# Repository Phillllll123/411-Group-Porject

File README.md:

# 411-Group-Porject
Group 3
git add

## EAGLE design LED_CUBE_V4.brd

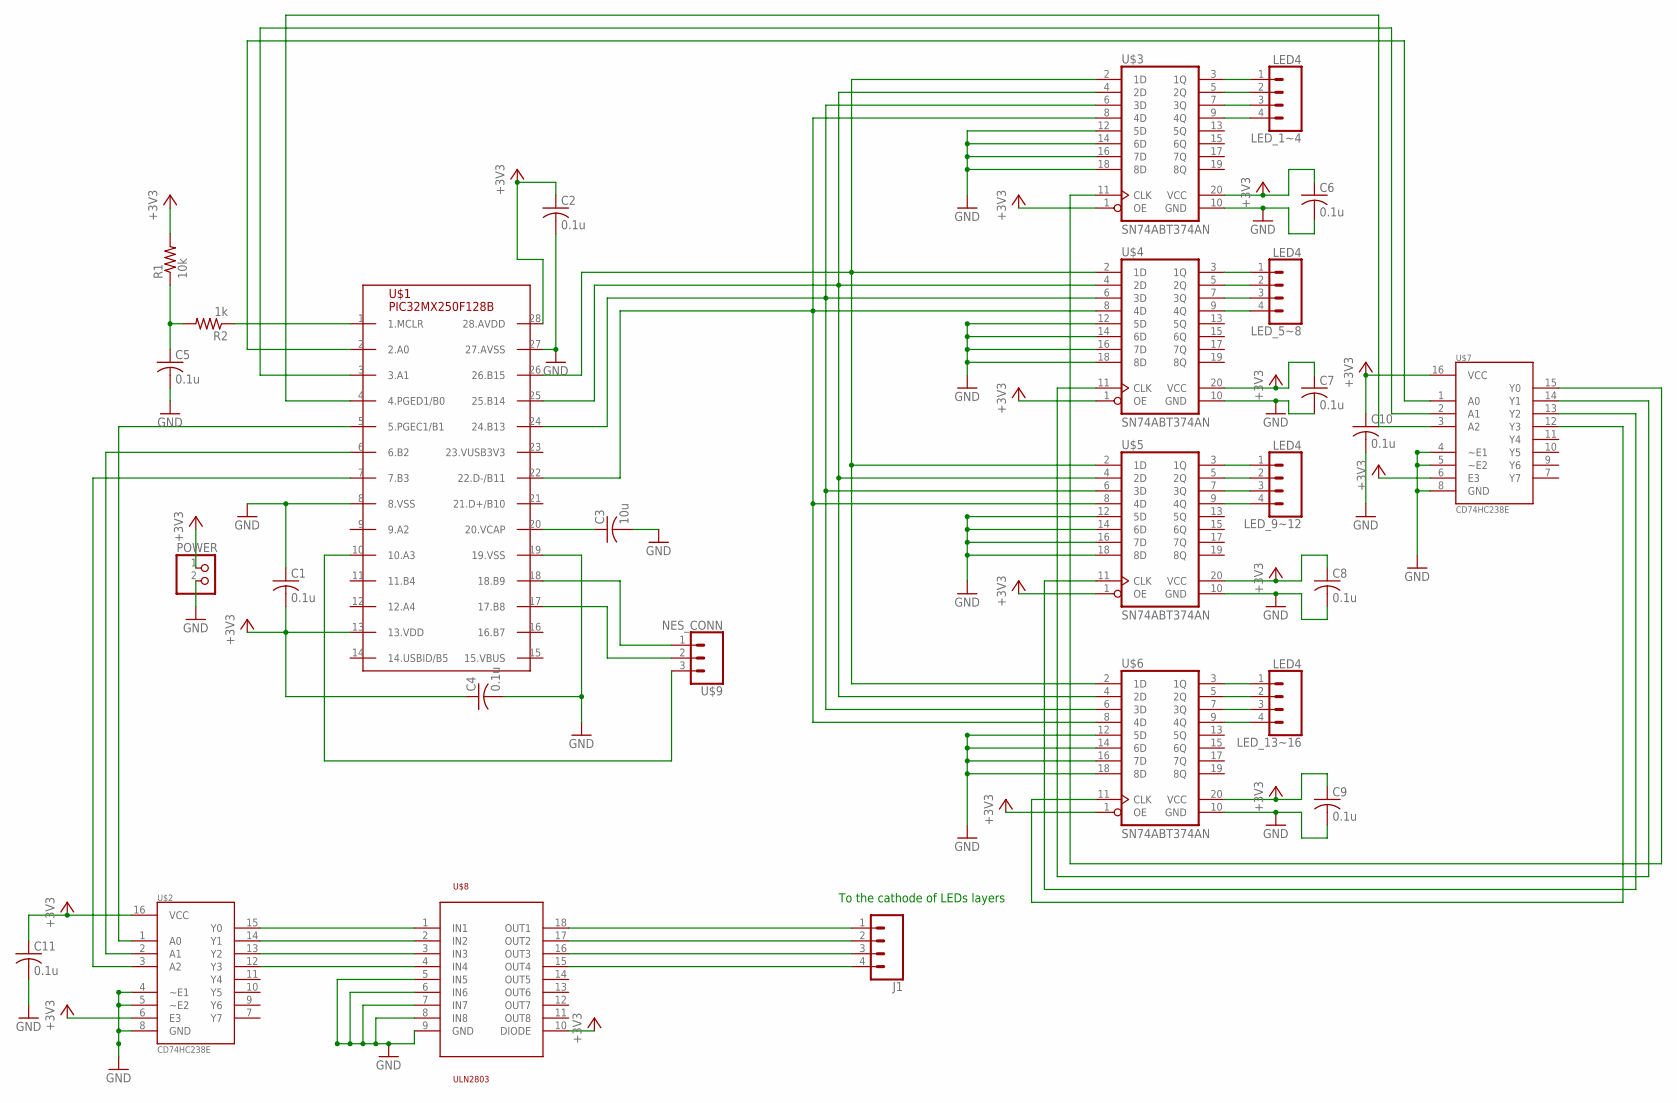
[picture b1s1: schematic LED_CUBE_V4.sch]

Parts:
C1, C2, C4, C5, C6, C7, C8, C9, C10, C11: 0.1u; C025-025X050
C3: 10u; C025-025X050
J1: CONN_04; 1X04
LED_1~4, LED_5~8, LED_9~12, LED_13~16: LED4; 1X04
POWER: PINHD-1X2; 1X02
R1: 10k; 0204/7
R2: 1k; 0204/7
U$1: PIC32MX250F128B; DIL28-3
U$2, U$7: CD74HC238E; DIL16
U$3, U$4, U$5, U$6: SN74ABT374AN; DIL20
U$8: ULN2803; SO18L
U$9: NES_CONN; 1X03

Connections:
+3V3: C1.2, C2.1, C4.1, C6.1, C7.1, C8.1, C9.1, C10.1, C11.1, POWER.1, R1.2, U$1.13 (13.VDD), U$1.28 (28.AVDD), U$2.6 (E3), U$2.16 (VCC), U$3.1 (OE), U$3.20 (VCC), U$4.1 (OE), U$4.20 (VCC), U$5.1 (OE), U$5.20 (VCC), U$6.1 (OE), U$6.20 (VCC), U$7.6 (E3), U$7.16 (VCC), U$8.10 (DIODE)
GND: C1.1, C2.2, C3.2, C4.2, C5.2, C6.2, C7.2, C8.2, C9.2, C10.2, C11.2, POWER.2, U$1.8 (8.VSS), U$1.19 (19.VSS), U$1.27 (27.AVSS), U$2.4 (~E1), U$2.5 (~E2), U$2.8 (GND), U$3.10 (GND), U$3.12 (5D), U$3.14 (6D), U$3.16 (7D), U$3.18 (8D), U$4.10 (GND), U$4.12 (5D), U$4.14 (6D), U$4.16 (7D), U$4.18 (8D), U$5.10 (GND), U$5.12 (5D), U$5.14 (6D), U$5.16 (7D), U$5.18 (8D), U$6.10 (GND), U$6.12 (5D), U$6.14 (6D), U$6.16 (7D), U$6.18 (8D), U$7.4 (~E1), U$7.5 (~E2), U$7.8 (GND), U$8.5 (IN5), U$8.6 (IN6), U$8.7 (IN7), U$8.8 (IN8), U$8.9 (GND)
LED1: LED_1~4.1, U$3.3 (1Q)
unnamed: U$2.15 (Y0), U$8.1 (IN1)
unnamed: U$2.14 (Y1), U$8.2 (IN2)
unnamed: U$2.13 (Y2), U$8.3 (IN3)
unnamed: U$2.12 (Y3), U$8.4 (IN4)
unnamed: U$1.10 (10.A3), U$9.3
unnamed: U$1.17 (17.B8), U$9.2
unnamed: U$1.18 (18.B9), U$9.1
unnamed: J1.1, U$8.18 (OUT1)
unnamed: J1.2, U$8.17 (OUT2)
unnamed: J1.3, U$8.16 (OUT3)
unnamed: J1.4, U$8.15 (OUT4)
unnamed: C3.1, U$1.20 (20.VCAP)
unnamed: U$1.5 (5.PGEC1/B1), U$2.1 (A0)
unnamed: U$1.6 (6.B2), U$2.2 (A1)
unnamed: U$1.7 (7.B3), U$2.3 (A2)
unnamed: LED_9~12.1, U$5.3 (1Q)
unnamed: U$1.26 (26.B15), U$3.2 (1D), U$4.2 (1D), U$5.2 (1D), U$6.2 (1D)
unnamed: U$1.25 (25.B14), U$3.4 (2D), U$4.4 (2D), U$5.4 (2D), U$6.4 (2D)
unnamed: U$1.22 (22.D-/B11), U$3.8 (4D), U$4.8 (4D), U$5.8 (4D), U$6.8 (4D)
unnamed: U$1.24 (24.B13), U$3.6 (3D), U$4.6 (3D), U$5.6 (3D), U$6.6 (3D)
unnamed: C5.1, R1.1, R2.2
unnamed: R2.1, U$1.1 (1.MCLR)
unnamed: U$3.11 (CLK), U$7.15 (Y0)
unnamed: U$4.11 (CLK), U$7.14 (Y1)
unnamed: U$1.3 (3.A1), U$7.2 (A1)
unnamed: U$1.4 (4.PGED1/B0), U$7.3 (A2)
unnamed: U$5.11 (CLK), U$7.13 (Y2)
unnamed: U$6.11 (CLK), U$7.12 (Y3)
unnamed: LED_9~12.2, U$5.5 (2Q)
unnamed: U$1.2 (2.A0), U$7.1 (A0)
unnamed: LED_1~4.2, U$3.5 (2Q)
unnamed: LED_1~4.3, U$3.7 (3Q)
unnamed: LED_1~4.4, U$3.9 (4Q)
unnamed: LED_9~12.3, U$5.7 (3Q)
unnamed: LED_9~12.4, U$5.9 (4Q)
unnamed: LED_5~8.1, U$4.3 (1Q)
unnamed: LED_5~8.2, U$4.5 (2Q)
unnamed: LED_5~8.3, U$4.7 (3Q)
unnamed: LED_5~8.4, U$4.9 (4Q)
unnamed: LED_13~16.1, U$6.3 (1Q)
unnamed: LED_13~16.2, U$6.5 (2Q)
unnamed: LED_13~16.3, U$6.7 (3Q)
unnamed: LED_13~16.4, U$6.9 (4Q)

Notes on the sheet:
To the cathode of LEDs layers

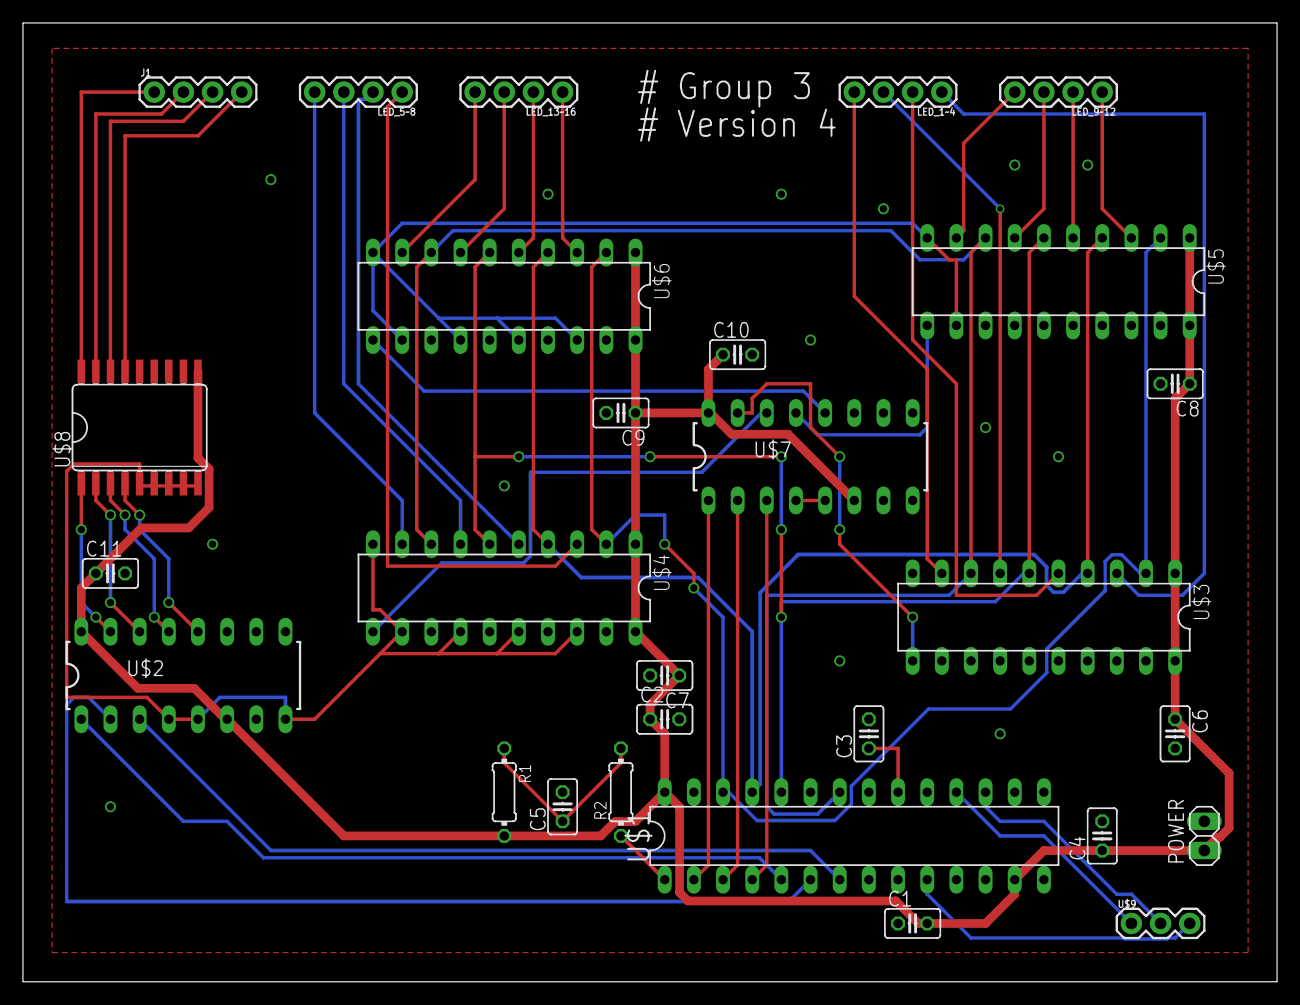
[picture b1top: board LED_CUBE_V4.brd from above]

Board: 2 copper layers, 109.2 x 83.5 mm, 28 parts (0 on the bottom side), 46 nets.

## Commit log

2017-11-10 Add files via upload
    I think we need replace the d-flipflop. The SN74ABT374AN is too difficult to layout.
2017-11-14 Rename CIRCUIT SCHEMATIC.brd to Layout.brd

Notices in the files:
parts and their libraries:
SparkFun-Connectors: Licensing: Creative Commons ShareAlike 4.0 International - https://creativecommons.org/licenses/by-sa/4.0
